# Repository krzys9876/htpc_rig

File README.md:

# Home entertainment rig

This is a dump of various files related to the devices that I use in my home entertainment setup. 

## HTPC

A miniITX PC enclosed in custom case (see: [modushop.pl](https://www.modushop.pl/)). The PC is fanless, so I had to choose a relative low power processor and a good radiator. However, since I have a overhead projector with a loud fan it doesn't matter at all.

## Volumio player

A Raspberry Pi based Volumio player (see: [volumio.com](https://volumio.com)) enclosed in custom case. There are two Pis: one is a controller for two displays, the other is the actual player.

The controller uses a quick and dirty python script (it needs refactoring and one day I will do it).

## Power amp

Generally it works but I had to remove the power meters as it wasn't a good idea. Now I'm thinking about something different.

## Power supply

This was done just for fun - two DC suppies (5V, 12V) in a custom case with meters and fancy switches. Nothing super complicated, I just wanted to have a power supply of a concise look instead of a bunch of random wall socket supplies.

## Preamp

The purpose of this was actually to make a super fancy relay-based attenuator with custom arduino-like controller. So much fun when building, maybe not that much when using it but who cares, this is what DIY is all about.

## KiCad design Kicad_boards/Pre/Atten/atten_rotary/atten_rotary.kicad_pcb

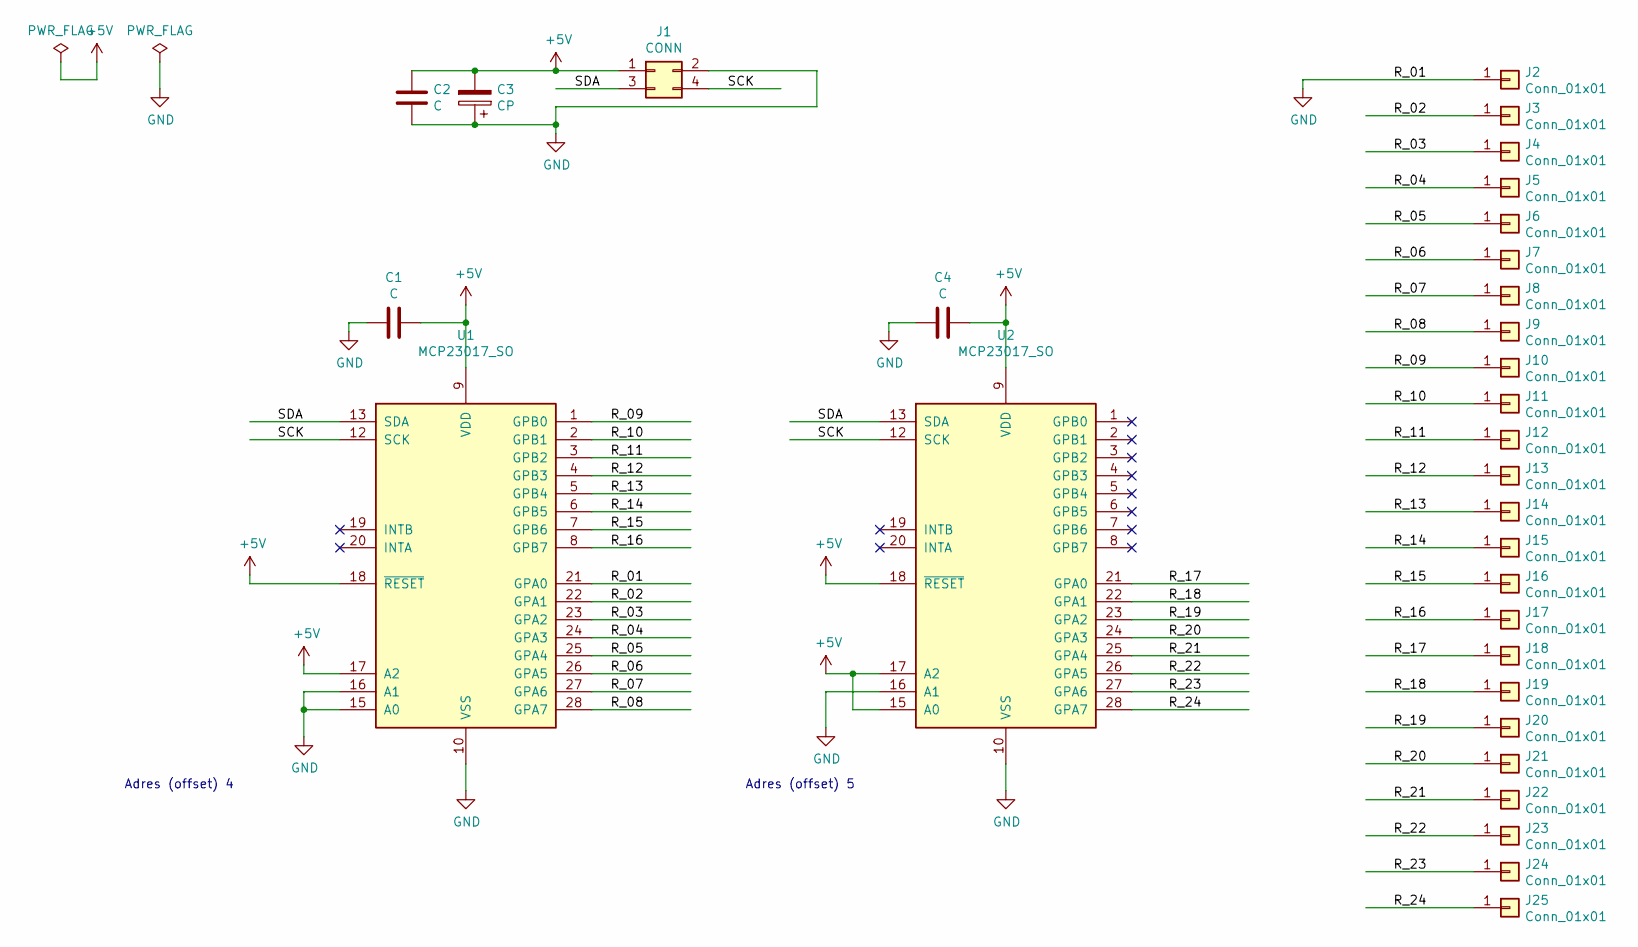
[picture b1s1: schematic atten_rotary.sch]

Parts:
C1, C2, C4: C; C_1206_3216Metric
C3: CP; C_1812_4532Metric
J1: CONN; PinHeader_2x02_P2.54mm_Vertical
J2, J3, J4, J5, J6, J7, J8, J9, J10, J11, J12, J13, J14, J15, J16, J17, J18, J19, J20, J21, J22, J23, J24, J25: Conn_01x01; PinHeader_1x01_P2.54mm_Vertical
U1, U2: MCP23017_SO; SOIC-28W_7.5x17.9mm_P1.27mm

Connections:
+5V: C1.2, C2.1, C3.2, C4.2, J1.1, U1.9 (VDD), U1.17 (A2), U1.18 (~RESET~), U2.9 (VDD), U2.15 (A0), U2.17 (A2), U2.18 (~RESET~)
/R_02: J3.1, U1.22 (GPA1)
/R_03: J4.1, U1.23 (GPA2)
/R_04: J5.1, U1.24 (GPA3)
/R_05: J6.1, U1.25 (GPA4)
/R_06: J7.1, U1.26 (GPA5)
/R_07: J8.1, U1.27 (GPA6)
/R_08: J9.1, U1.28 (GPA7)
/R_09: J10.1, U1.1 (GPB0)
/R_10: J11.1, U1.2 (GPB1)
/R_11: J12.1, U1.3 (GPB2)
/R_12: J13.1, U1.4 (GPB3)
/R_13: J14.1, U1.5 (GPB4)
/R_14: J15.1, U1.6 (GPB5)
/R_15: J16.1, U1.7 (GPB6)
/R_16: J17.1, U1.8 (GPB7)
/R_17: J18.1, U2.21 (GPA0)
/R_18: J19.1, U2.22 (GPA1)
/R_19: J20.1, U2.23 (GPA2)
/R_20: J21.1, U2.24 (GPA3)
/R_21: J22.1, U2.25 (GPA4)
/R_22: J23.1, U2.26 (GPA5)
/R_23: J24.1, U2.27 (GPA6)
/R_24: J25.1, U2.28 (GPA7)
/SCK: J1.4, U1.12 (SCK), U2.12 (SCK)
/SDA: J1.3, U1.13 (SDA), U2.13 (SDA)
GND: C1.1, C2.2, C3.1, C4.1, J1.2, J2.1, U1.10 (VSS), U1.15 (A0), U1.16 (A1), U1.21 (GPA0), U2.10 (VSS), U2.16 (A1); also elsewhere on the board

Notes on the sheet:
Adres (offset) 5
Adres (offset) 4

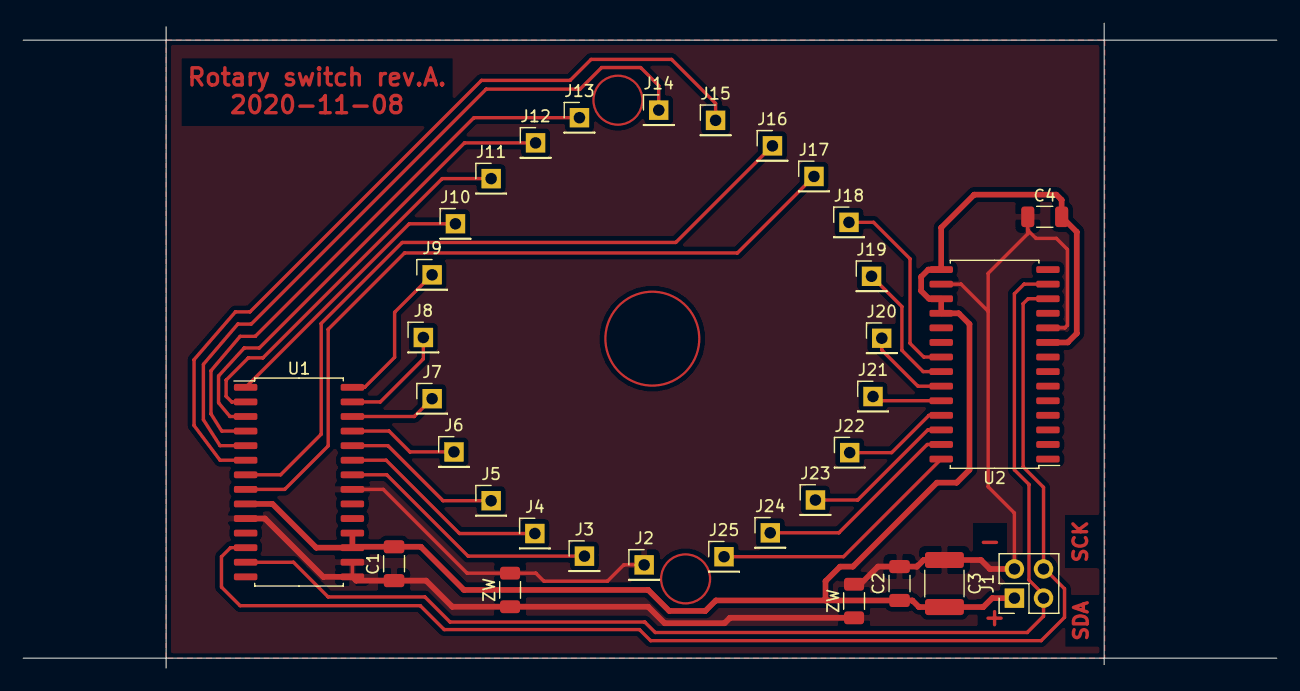
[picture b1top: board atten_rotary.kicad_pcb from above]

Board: 2 copper layers, 109.2 x 56.2 mm, 33 parts (0 on the bottom side), 27 nets.

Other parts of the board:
ZW: R_1206_3216Metric
ZW#2: 0; R_1206_3216Metric

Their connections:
GND: ZW.1, ZW.2, ZW#2.1, ZW#2.2; also elsewhere on the board

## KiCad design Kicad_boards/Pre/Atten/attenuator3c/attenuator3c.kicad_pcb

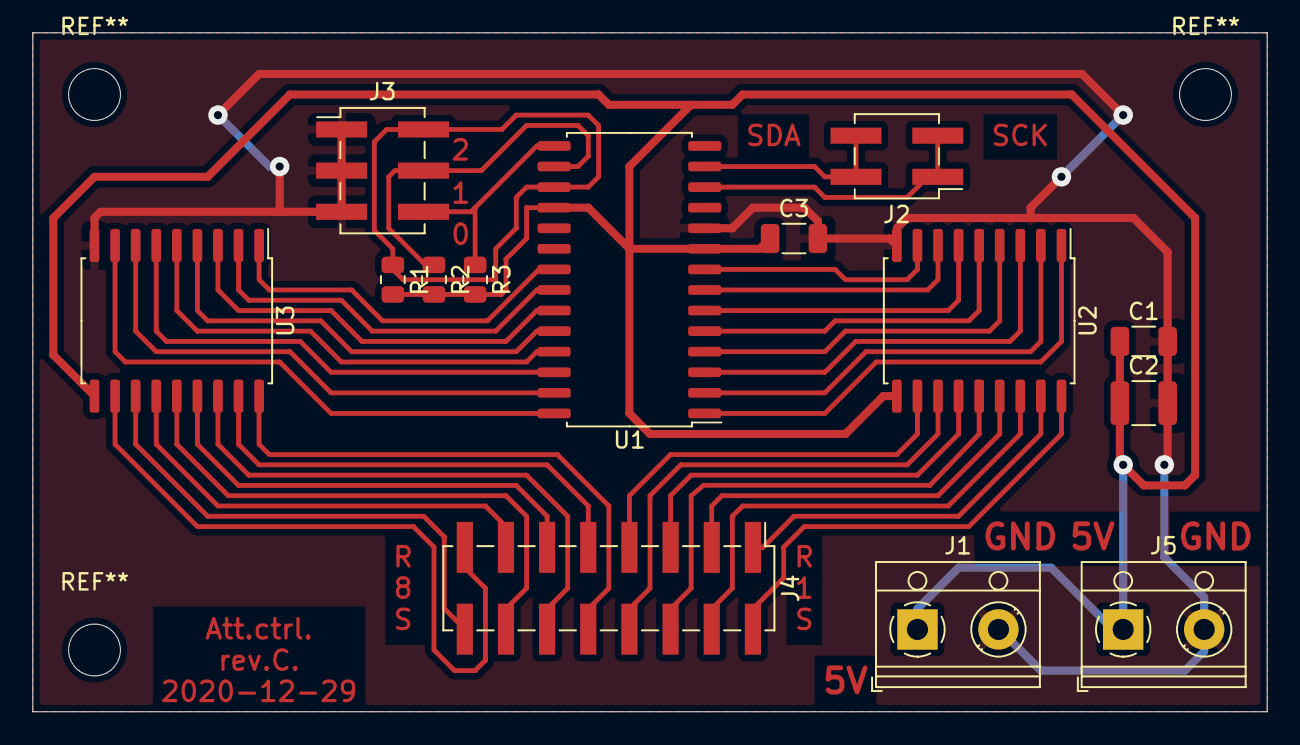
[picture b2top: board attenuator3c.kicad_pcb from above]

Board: 2 copper layers, 76.2 x 41.9 mm, 14 parts (0 on the bottom side), 39 nets.

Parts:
C1, C3: 100n; C_1206_3216Metric
C2: 10u; C_1210_3225Metric
J1: POWER; TerminalBlock_RND_205-00012_1x02_P5.00mm_Horizontal
J2: I2C; PinHeader_2x02_P2.54mm_Vertical_SMD
J3: Conn_Addr; PinHeader_2x03_P2.54mm_Vertical_SMD
J4: RELAY; PinHeader_2x08_P2.54mm_Vertical_SMD
J5: POWER2; TerminalBlock_RND_205-00012_1x02_P5.00mm_Horizontal
R1, R2, R3: R; R_0805_2012Metric
U1: MCP23017_SO; SOIC-28W_7.5x17.9mm_P1.27mm
U2, U3: ULN2803A; SOIC-18W_7.5x11.6mm_P1.27mm

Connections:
+5V: C1.1, C2.1, C3.1, J1.1, J5.1, R1.2, R2.2, R3.2, U1.9, U1.18, U2.10, U3.10
/R1_R: J4.1, U2.17
/R1_S: J4.2, U2.18
/R2_R: J4.3, U2.15
/R2_S: J4.4, U2.16
/R3_R: J4.5, U2.13
/R3_S: J4.6, U2.14
/R4_R: J4.7, U2.11
/R4_S: J4.8, U2.12
/R5_R: J4.9, U3.17
/R5_S: J4.10, U3.18
/R6_R: J4.11, U3.15
/R6_S: J4.12, U3.16
/R7_R: J4.13, U3.13
/R7_S: J4.14, U3.14
/R8_R: J4.15, U3.11
/R8_S: J4.16, U3.12
/SCK: J2.1, J2.3, U1.12
/SDA: J2.2, J2.4, U1.13
GND: C1.2, C2.2, C3.2, J1.2, J3.1, J3.3, J3.5, J5.2, U1.10, U2.9, U3.9
unnamed: J3.2, R1.1, U1.17
unnamed: J3.4, R2.1, U1.16
unnamed: J3.6, R3.1, U1.15
unnamed: U1.1, U2.1
unnamed: U1.2, U2.2
unnamed: U1.3, U2.3
unnamed: U1.4, U2.4
unnamed: U1.5, U2.5
unnamed: U1.6, U2.6
unnamed: U1.7, U2.7
unnamed: U1.8, U2.8
unnamed: U1.21, U3.1
unnamed: U1.22, U3.2
unnamed: U1.23, U3.3
unnamed: U1.24, U3.4
unnamed: U1.25, U3.5
unnamed: U1.26, U3.6
unnamed: U1.27, U3.7
unnamed: U1.28, U3.8

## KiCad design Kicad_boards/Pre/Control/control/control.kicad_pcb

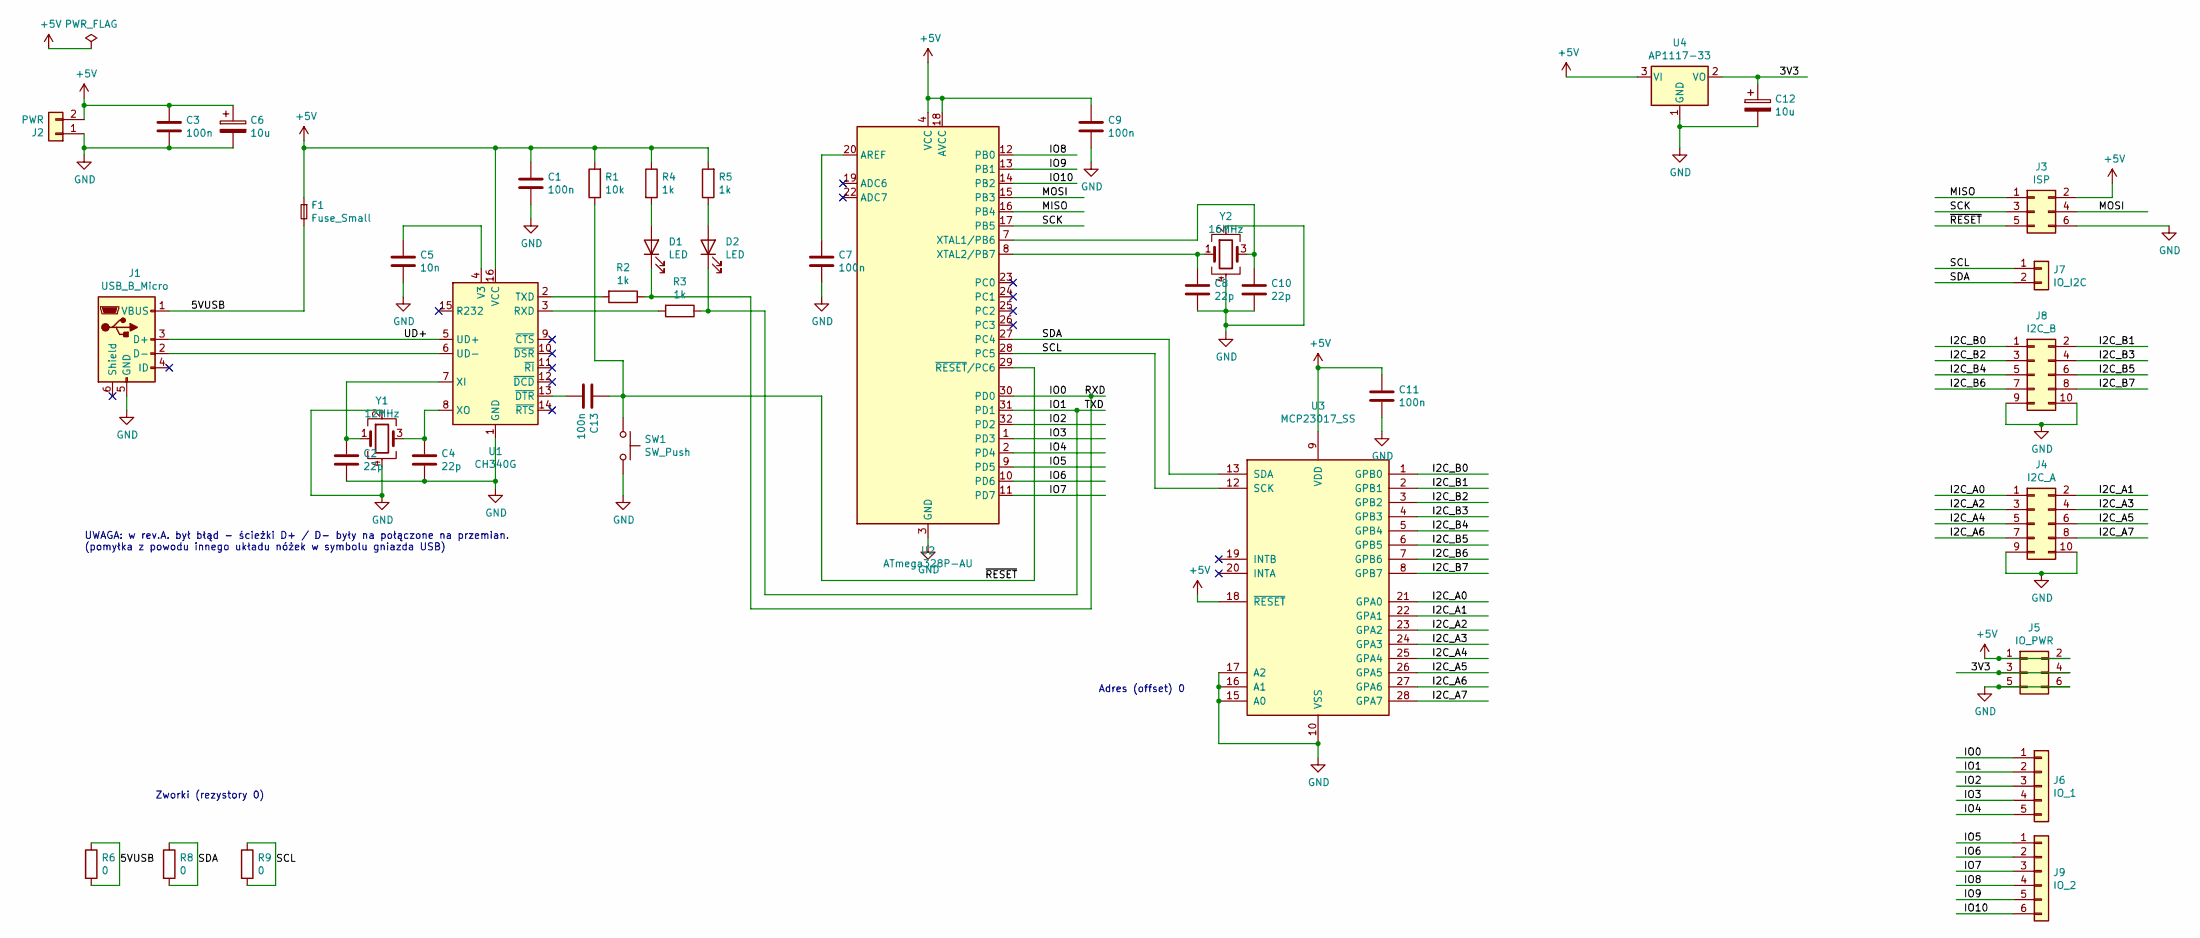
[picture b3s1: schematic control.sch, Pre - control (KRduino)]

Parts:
C1, C3, C7, C9, C11: 100n; C_1206_3216Metric
C2, C4, C8, C10: 22p; C_0603_1608Metric
C5: 10n; C_1206_3216Metric
C6, C12: 10u; C_1206_3216Metric
C13: 100n; C_0805_2012Metric
D1, D2: LED; D_0805_2012Metric
F1: Fuse_Small; Fuse_1812_4532Metric
J1: USB_B_Micro; USB_Micro-B_Amphenol_10104110_Horizontal
J2: PWR; TerminalBlock_RND_205-00001_1x02_P5.00mm_Horizontal
J3: ISP; PinHeader_2x03_P2.54mm_Vertical
J4: I2C_A; PinHeader_2x05_P2.54mm_Vertical
J5: IO_PWR; PinHeader_2x03_P2.54mm_Vertical
J6: IO_1; PinHeader_1x05_P2.54mm_Vertical
J7: IO_I2C; PinHeader_1x02_P2.54mm_Vertical
J8: I2C_B; PinHeader_2x05_P2.54mm_Vertical
J9: IO_2; PinHeader_1x06_P2.54mm_Vertical
R1: 10k; R_0805_2012Metric
R2, R3, R4, R5: 1k; R_0805_2012Metric
R6, R8, R9: 0; R_0805_2012Metric
SW1: SW_Push; SW_SPST_FSMSM
U1: CH340G; SOIC-16_3.9x9.9mm_P1.27mm
U2: ATmega328P-AU; TQFP-32_7x7mm_P0.8mm
U3: MCP23017_SS; SSOP-28_5.3x10.2mm_P0.65mm
U4: AP1117-33; SOT-223-3_TabPin2
Y1: 12MHz; Crystal_SMD_3225-4Pin_3.2x2.5mm
Y2: 16MHz; Crystal_SMD_3225-4Pin_3.2x2.5mm

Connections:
+5V: C1.1, C3.1, C6.1, C9.1, C11.1, F1.1, J2.2, J3.2, J5.1, J5.2, R1.2, R4.1, R5.2, U1.16 (VCC), U2.4 (VCC), U2.6 (VCC), U2.18 (AVCC), U3.9 (VDD), U3.18 (~RESET~), U4.3 (VI)
/3V3: C12.1, J5.3, J5.4, U4.2 (VO)
/5VUSB: F1.2, J1.1 (VBUS), R6.1, R6.2
/I2C_A0: J4.1, U3.21 (GPA0)
/I2C_A1: J4.2, U3.22 (GPA1)
/I2C_A2: J4.3, U3.23 (GPA2)
/I2C_A3: J4.4, U3.24 (GPA3)
/I2C_A4: J4.5, U3.25 (GPA4)
/I2C_A5: J4.6, U3.26 (GPA5)
/I2C_A6: J4.7, U3.27 (GPA6)
/I2C_A7: J4.8, U3.28 (GPA7)
/I2C_B0: J8.1, U3.1 (GPB0)
/I2C_B1: J8.2, U3.2 (GPB1)
/I2C_B2: J8.3, U3.3 (GPB2)
/I2C_B3: J8.4, U3.4 (GPB3)
/I2C_B4: J8.5, U3.5 (GPB4)
/I2C_B5: J8.6, U3.6 (GPB5)
/I2C_B6: J8.7, U3.7 (GPB6)
/I2C_B7: J8.8, U3.8 (GPB7)
/IO0: D1.1 (K), J6.1, R2.1, U2.30 (PD0)
/IO1: D2.1 (K), J6.2, R3.1, U2.31 (PD1)
/IO2: J6.3, U2.32 (PD2)
/IO3: J6.4, U2.1 (PD3)
/IO4: J6.5, U2.2 (PD4)
/IO5: J9.1, U2.9 (PD5)
/IO6: J9.2, U2.10 (PD6)
/IO7: J9.3, U2.11 (PD7)
/IO8: J9.4, U2.12 (PB0)
/IO9: J9.5, U2.13 (PB1)
/IO10: J9.6, U2.14 (PB2)
/MISO: J3.1, U2.16 (PB4)
/MOSI: J3.4, U2.15 (PB3)
/SCK: J3.3, U2.17 (PB5)
/SCL: J7.1, R9.1, R9.2, U2.28 (PC5), U3.12 (SCK)
/SDA: J7.2, R8.1, R8.2, U2.27 (PC4), U3.13 (SDA)
/UD+: J1.3 (D+), U1.5 (UD+)
/~RESET: C13.1, J3.5, R1.1, SW1.1, U2.29 (~RESET~/PC6)
GND: C1.2, C2.2, C3.2, C4.2, C5.1, C6.2, C7.2, C8.2, C9.2, C10.2, C11.2, C12.2, J1.5 (GND), J2.1, J3.6, J4.9, J4.10, J5.5, J5.6, J8.9, J8.10, SW1.2, U1.1 (GND), U2.3 (GND), U2.5 (GND), U2.21 (GND), U3.10 (VSS), U3.15 (A0), U3.16 (A1), U3.17 (A2), U4.1 (GND), Y1.2, Y1.4, Y2.2, Y2.4
unnamed: C2.1, U1.7 (XI), Y1.1
unnamed: C4.1, U1.8 (XO), Y1.3
unnamed: C5.2, U1.4 (V3)
unnamed: C7.1, U2.20 (AREF)
unnamed: C8.1, U2.8 (XTAL2/PB7), Y2.1
unnamed: C10.1, U2.7 (XTAL1/PB6), Y2.3
unnamed: C13.2, U1.13 (~DTR)
unnamed: D1.2 (A), R4.2
unnamed: D2.2 (A), R5.1
unnamed: J1.2 (D-), U1.6 (UD-)
unnamed: R2.2, U1.2 (TXD)
unnamed: R3.2, U1.3 (RXD)

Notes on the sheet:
Zworki (rezystory 0)
UWAGA: w rev.A. był błąd - ścieżki D+ / D- były na połączone na przemian. (pomyłka z powodu innego układu nóżek w symbolu gniazda USB)
Adres (offset) 0

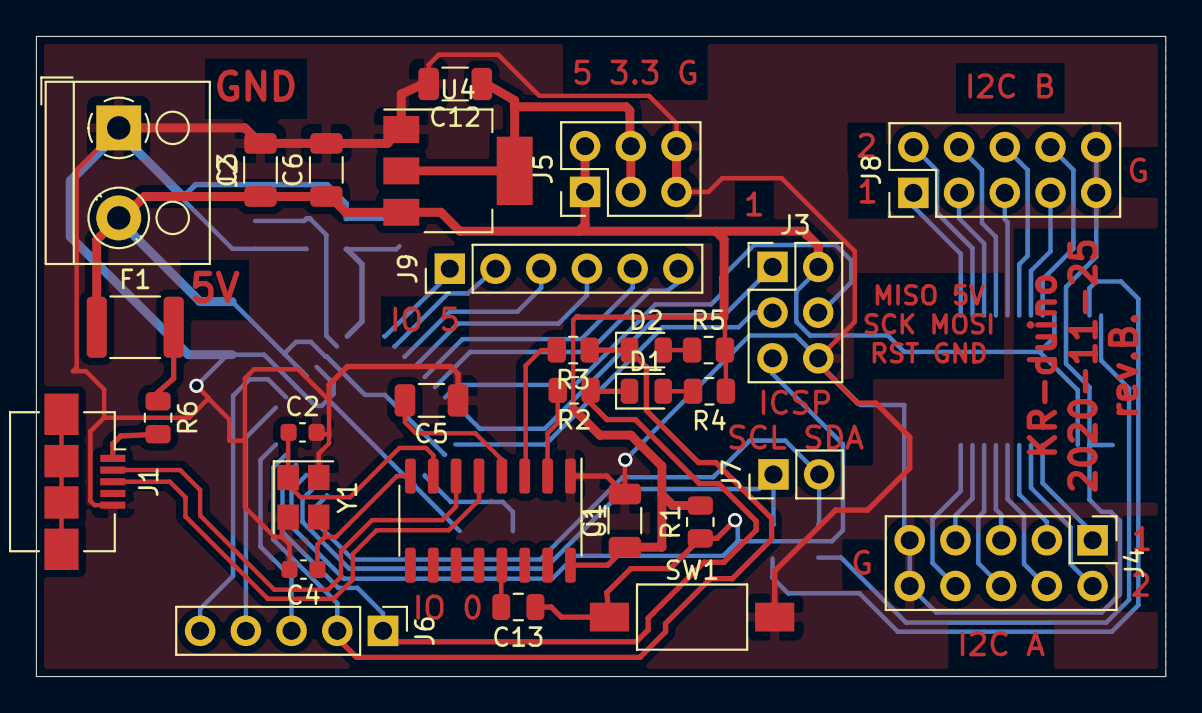
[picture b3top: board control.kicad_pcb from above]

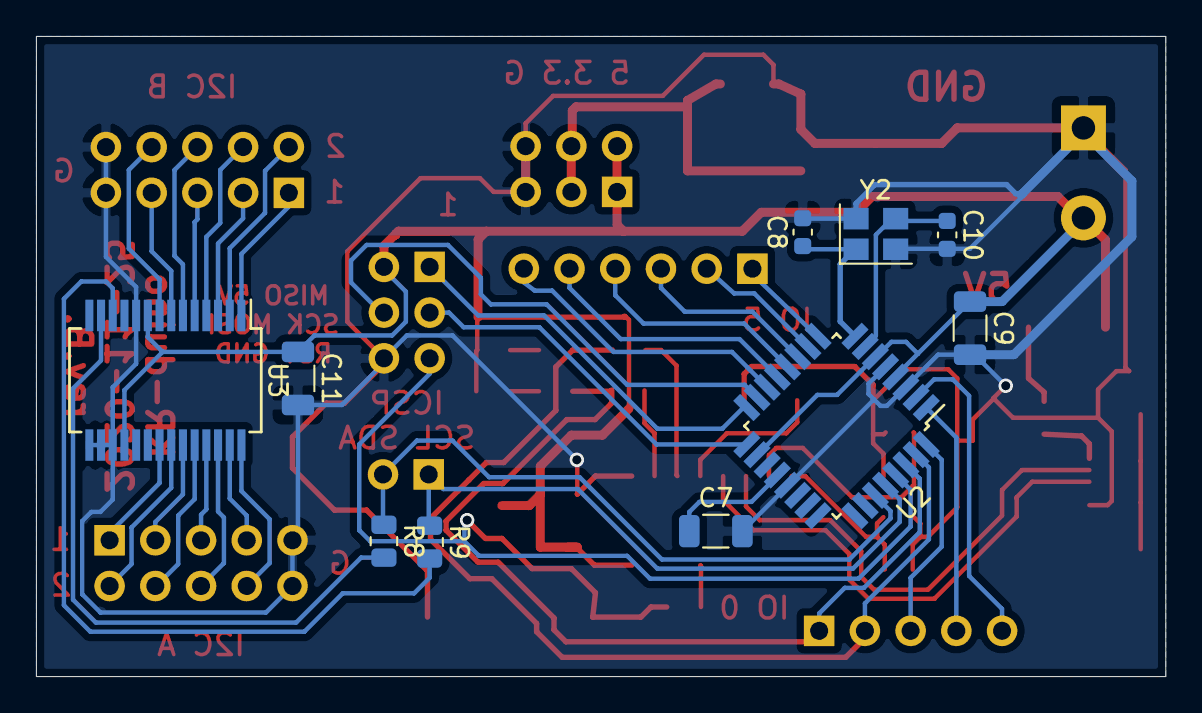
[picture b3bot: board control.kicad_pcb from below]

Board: 2 copper layers, 62.7 x 35.6 mm, 40 parts (10 on the bottom side), 50 nets.

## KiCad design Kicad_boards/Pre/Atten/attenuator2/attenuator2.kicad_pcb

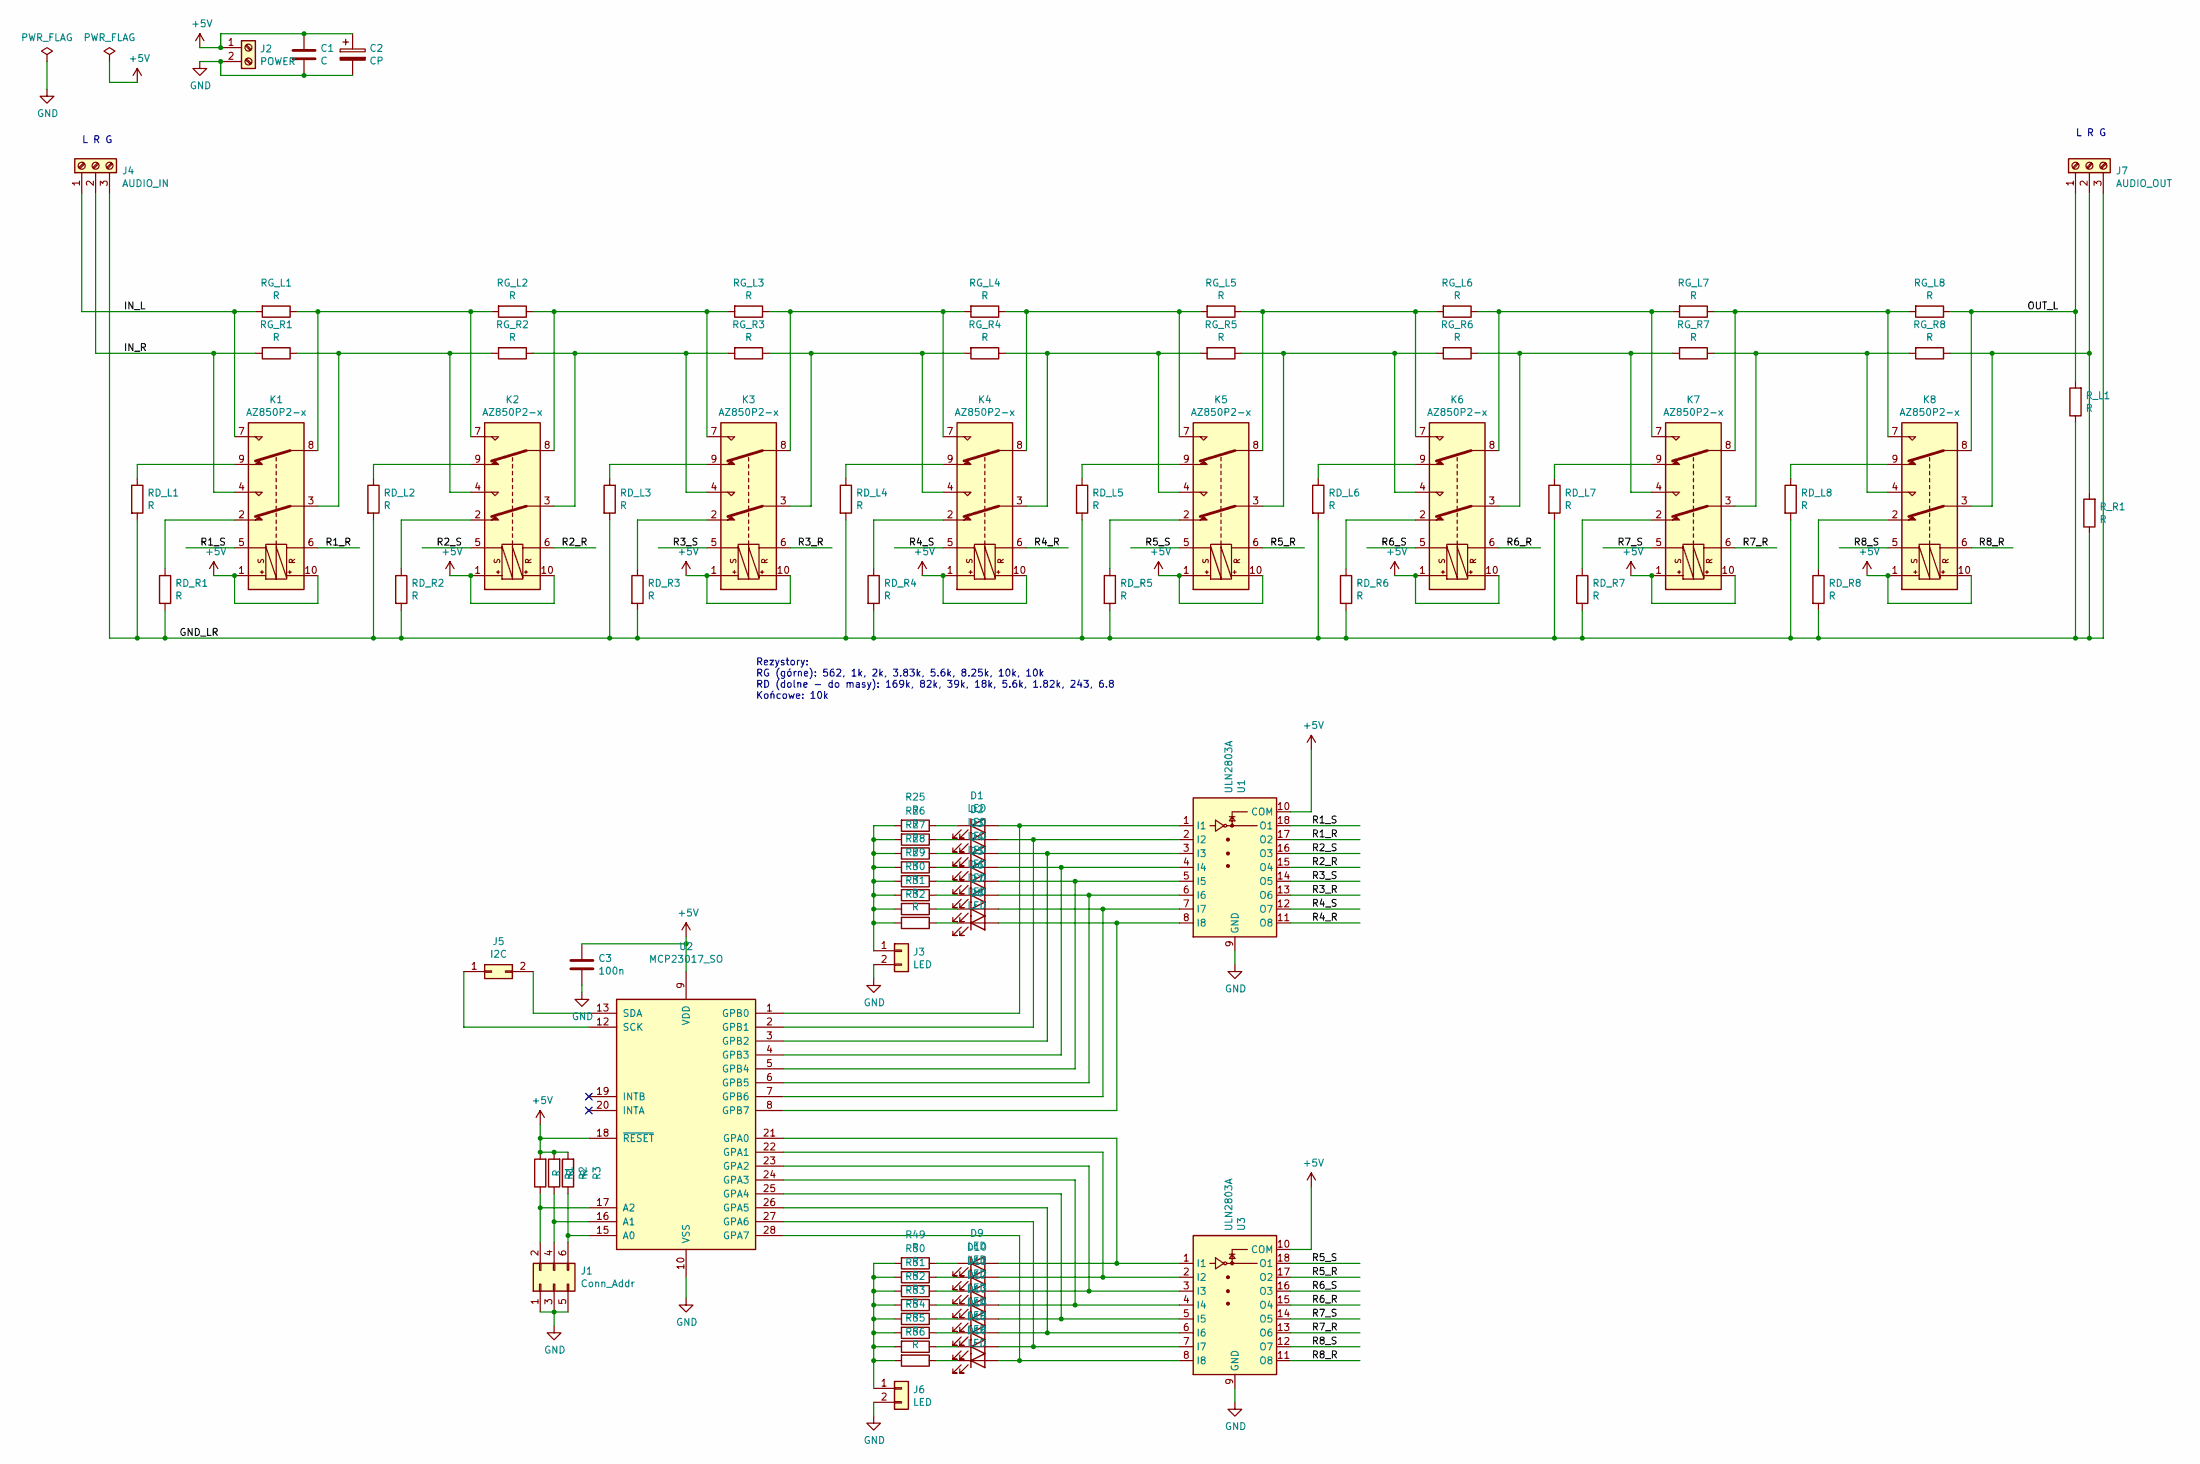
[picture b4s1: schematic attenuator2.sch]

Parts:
C1: C; C_1206_3216Metric
C2: CP; C_1210_3225Metric
C3: 100n; C_1206_3216Metric
D1, D2, D3, D4, D5, D6, D7, D8, D9, D10, D11, D12, D13, D14, D15, D16: LED; LED_0805_2012Metric
J1: Conn_Addr; PinHeader_2x03_P2.54mm_Vertical
J2: POWER; TerminalBlock_RND_205-00012_1x02_P5.00mm_Horizontal
J3, J6: LED; PinHeader_1x02_P2.54mm_Vertical
J4: AUDIO_IN; TerminalBlock_RND_205-00013_1x03_P5.00mm_Horizontal
J5: I2C; PinHeader_2x01_P2.54mm_Vertical_SMD
J7: AUDIO_OUT; TerminalBlock_RND_205-00013_1x03_P5.00mm_Horizontal
K1, K2, K3, K4, K5, K6, K7, K8: AZ850P2-x; Relay_DPDT_FRT5
R1, R2, R3, R25, R26, R27, R28, R29, R30, R31, R32, R49, R50, R51, R52, R53, R54, R55, R56: R; R_0805_2012Metric
RD_L1, RD_L2, RD_L3, RD_L4, RD_L5, RD_L6, RD_L7, RD_L8: R; R_Axial_DIN0207_L6.3mm_D2.5mm_P10.16mm_Horizontal
RD_R1, RD_R2, RD_R3, RD_R4, RD_R5, RD_R6, RD_R7, RD_R8: R; R_Axial_DIN0207_L6.3mm_D2.5mm_P10.16mm_Horizontal
RG_L1, RG_L2, RG_L3, RG_L4, RG_L5, RG_L6, RG_L7, RG_L8: R; R_Axial_DIN0207_L6.3mm_D2.5mm_P10.16mm_Horizontal
RG_R1, RG_R2, RG_R3, RG_R4, RG_R5, RG_R6, RG_R7, RG_R8: R; R_Axial_DIN0207_L6.3mm_D2.5mm_P10.16mm_Horizontal
R_L1: R; R_Axial_DIN0207_L6.3mm_D2.5mm_P10.16mm_Horizontal
R_R1: R; R_Axial_DIN0207_L6.3mm_D2.5mm_P10.16mm_Horizontal
U1, U3: ULN2803A; SOIC-18W_7.5x11.6mm_P1.27mm
U2: MCP23017_SO; SOIC-28W_7.5x17.9mm_P1.27mm

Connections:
+5V: C1.1, C2.1, C3.1, J2.1, K1.1, K1.10, K2.1, K2.10, K3.1, K3.10, K4.1, K4.10, K5.1, K5.10, K6.1, K6.10, K7.1, K7.10, K8.1, K8.10, R1.2, R2.2, R3.2, U1.10 (COM), U2.9 (VDD), U2.18 (~RESET~), U3.10 (COM)
/GND_LR: J4.3, J7.3, RD_L1.2, RD_L2.2, RD_L3.2, RD_L4.2, RD_L5.2, RD_L6.2, RD_L7.2, RD_L8.2, RD_R1.2, RD_R2.2, RD_R3.2, RD_R4.2, RD_R5.2, RD_R6.2, RD_R7.2, RD_R8.2, R_L1.1, R_R1.1
/IN_L: J4.1, K1.7, RG_L1.2
/IN_R: J4.2, K1.4, RG_R1.2
/OUT_L: J7.1, K8.8, RG_L8.1, R_L1.2
/R1_R: K1.6, U1.17 (O2)
/R1_S: K1.5, U1.18 (O1)
/R2_R: K2.6, U1.15 (O4)
/R2_S: K2.5, U1.16 (O3)
/R3_R: K3.6, U1.13 (O6)
/R3_S: K3.5, U1.14 (O5)
/R4_R: K4.6, U1.11 (O8)
/R4_S: K4.5, U1.12 (O7)
/R5_R: K5.6, U3.17 (O2)
/R5_S: K5.5, U3.18 (O1)
/R6_R: K6.6, U3.15 (O4)
/R6_S: K6.5, U3.16 (O3)
/R7_R: K7.6, U3.13 (O6)
/R7_S: K7.5, U3.14 (O5)
/R8_R: K8.6, U3.11 (O8)
/R8_S: K8.5, U3.12 (O7)
GND: C1.2, C2.2, C3.2, J1.1, J1.3, J1.5, J2.2, J3.2, J6.2, U1.9 (GND), U2.10 (VSS), U3.9 (GND)
unnamed: D1.1 (K), R25.1
unnamed: D1.2 (A), U1.1 (I1), U2.1 (GPB0)
unnamed: D2.1 (K), R26.1
unnamed: D2.2 (A), U1.2 (I2), U2.2 (GPB1)
unnamed: D3.1 (K), R27.1
unnamed: D3.2 (A), U1.3 (I3), U2.3 (GPB2)
unnamed: D4.1 (K), R28.1
unnamed: D4.2 (A), U1.4 (I4), U2.4 (GPB3)
unnamed: D5.1 (K), R29.1
unnamed: D5.2 (A), U1.5 (I5), U2.5 (GPB4)
unnamed: D6.1 (K), R30.1
unnamed: D6.2 (A), U1.6 (I6), U2.6 (GPB5)
unnamed: D7.1 (K), R31.1
unnamed: D7.2 (A), U1.7 (I7), U2.7 (GPB6)
unnamed: D8.1 (K), R32.1
unnamed: D8.2 (A), U1.8 (I8), U2.8 (GPB7)
unnamed: D9.1 (K), R49.1
unnamed: D9.2 (A), U2.21 (GPA0), U3.1 (I1)
unnamed: D10.1 (K), R50.1
unnamed: D10.2 (A), U2.22 (GPA1), U3.2 (I2)
unnamed: D11.1 (K), R51.1
unnamed: D11.2 (A), U2.23 (GPA2), U3.3 (I3)
unnamed: D12.1 (K), R52.1
unnamed: D12.2 (A), U2.24 (GPA3), U3.4 (I4)
unnamed: D13.1 (K), R53.1
unnamed: D13.2 (A), U2.25 (GPA4), U3.5 (I5)
unnamed: D14.1 (K), R54.1
unnamed: D14.2 (A), U2.26 (GPA5), U3.6 (I6)
unnamed: D15.1 (K), R55.1
unnamed: D15.2 (A), U2.27 (GPA6), U3.7 (I7)
unnamed: D16.1 (K), R56.1
unnamed: D16.2 (A), U2.28 (GPA7), U3.8 (I8)
unnamed: J1.2, R1.1, U2.17 (A2)
unnamed: J1.4, R2.1, U2.16 (A1)
unnamed: J1.6, R3.1, U2.15 (A0)
unnamed: J3.1, R25.2, R26.2, R27.2, R28.2, R29.2, R30.2, R31.2, R32.2
unnamed: J5.1, U2.12 (SCK)
unnamed: J5.2, U2.13 (SDA)
unnamed: J6.1, R49.2, R50.2, R51.2, R52.2, R53.2, R54.2, R55.2, R56.2
unnamed: J7.2, K8.3, RG_R8.1, R_R1.2
unnamed: K1.2, RD_R1.1
unnamed: K1.3, K2.4, RG_R1.1, RG_R2.2
unnamed: K1.8, K2.7, RG_L1.1, RG_L2.2
unnamed: K1.9, RD_L1.1
unnamed: K2.2, RD_R2.1
unnamed: K2.3, K3.4, RG_R2.1, RG_R3.2
unnamed: K2.8, K3.7, RG_L2.1, RG_L3.2
unnamed: K2.9, RD_L2.1
unnamed: K3.2, RD_R3.1
unnamed: K3.3, K4.4, RG_R3.1, RG_R4.2
unnamed: K3.8, K4.7, RG_L3.1, RG_L4.2
unnamed: K3.9, RD_L3.1
unnamed: K4.2, RD_R4.1
unnamed: K4.3, K5.4, RG_R4.1, RG_R5.2
unnamed: K4.8, K5.7, RG_L4.1, RG_L5.2
unnamed: K4.9, RD_L4.1
unnamed: K5.2, RD_R5.1
unnamed: K5.3, K6.4, RG_R5.1, RG_R6.2
unnamed: K5.8, K6.7, RG_L5.1, RG_L6.2
unnamed: K5.9, RD_L5.1
unnamed: K6.2, RD_R6.1
unnamed: K6.3, K7.4, RG_R6.1, RG_R7.2
unnamed: K6.8, K7.7, RG_L6.1, RG_L7.2
unnamed: K6.9, RD_L6.1
unnamed: K7.2, RD_R7.1
unnamed: K7.3, K8.4, RG_R7.1, RG_R8.2
unnamed: K7.8, K8.7, RG_L7.1, RG_L8.2
unnamed: K7.9, RD_L7.1
unnamed: K8.2, RD_R8.1
unnamed: K8.9, RD_L8.1

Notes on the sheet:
Rezystory: RG (górne): 562, 1k, 2k, 3.83k, 5.6k, 8.25k, 10k, 10k RD (dolne - do masy): 169k, 82k, 39k, 18k, 5.6k, 1.82k, 243, 6.8 Końcowe: 10k
L R G

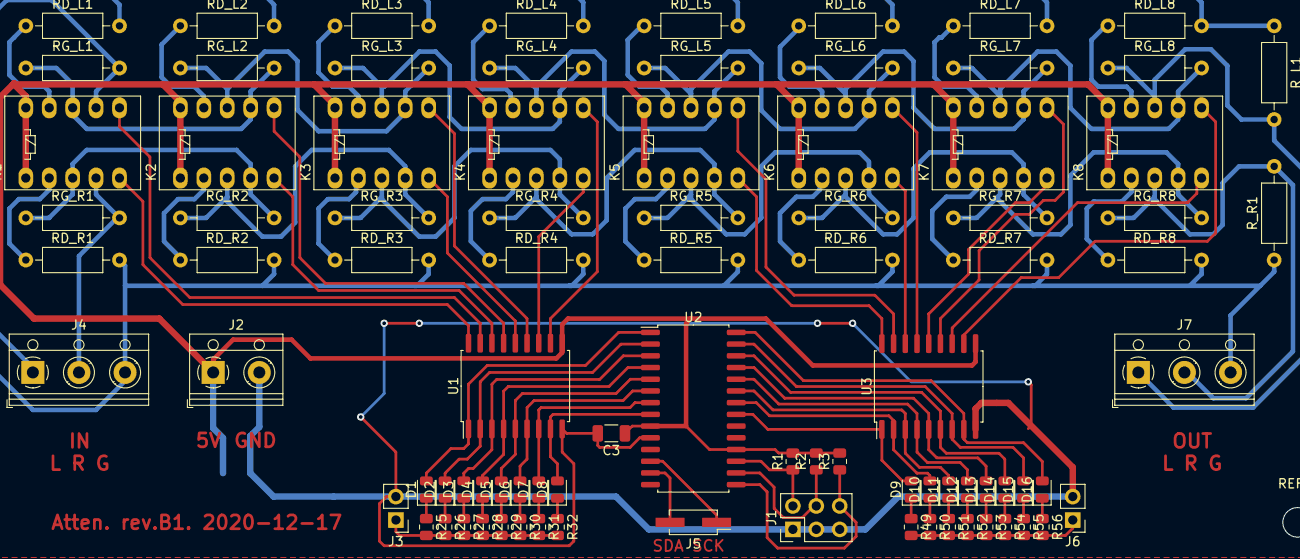
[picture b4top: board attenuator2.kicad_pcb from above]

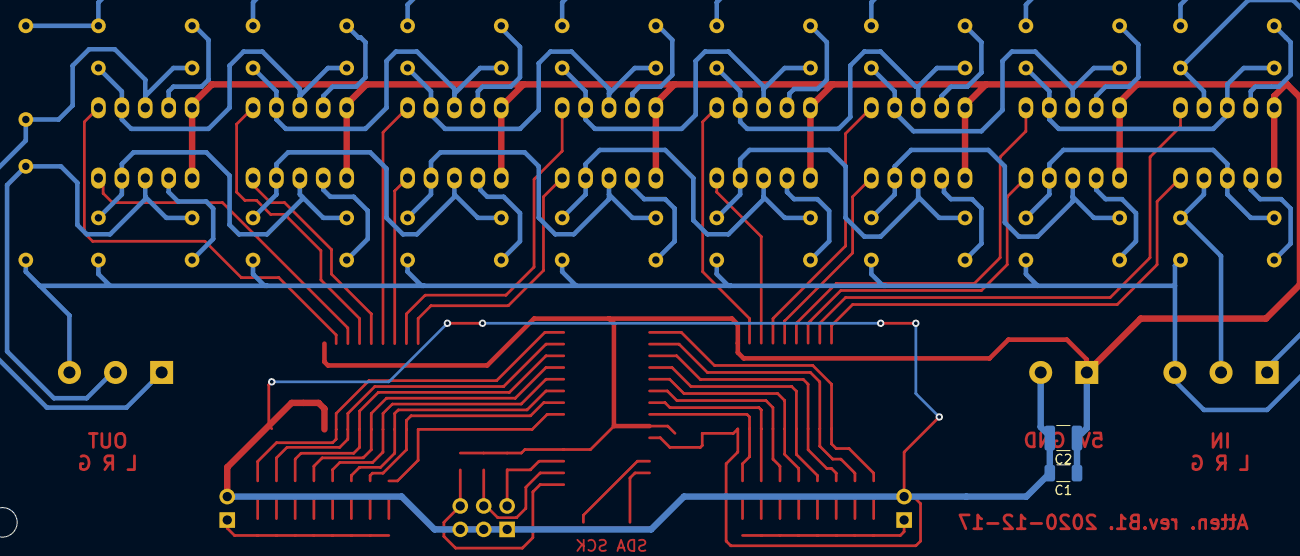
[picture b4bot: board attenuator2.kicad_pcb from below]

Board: 2 copper layers, 90 parts (2 on the bottom side), 92 nets.

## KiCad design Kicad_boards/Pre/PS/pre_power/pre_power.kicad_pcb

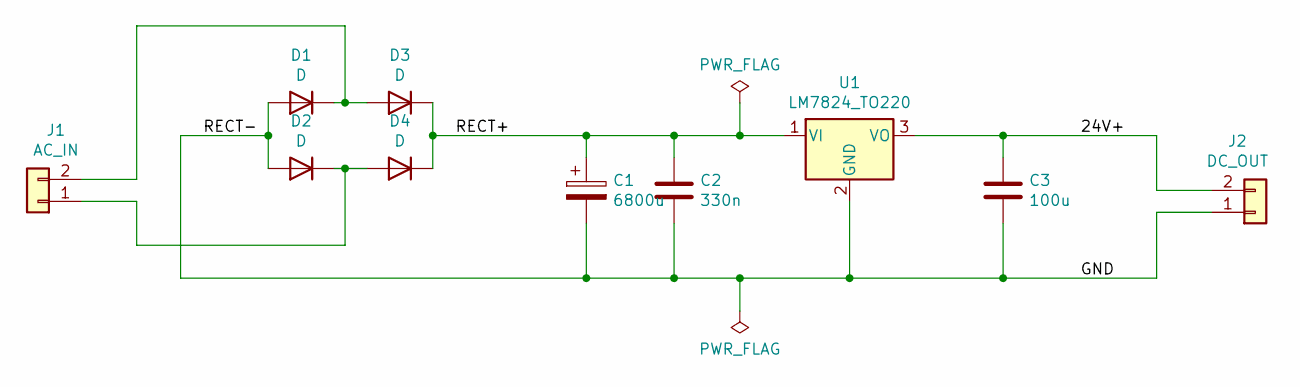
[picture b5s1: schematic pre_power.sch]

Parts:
C1: 6800u; TerminalBlock_RND_205-00001_1x02_P5.00mm_Horizontal
C2: 330n; C_Disc_D4.7mm_W2.5mm_P5.00mm
C3: 100u; C_Disc_D4.7mm_W2.5mm_P5.00mm
D1, D2, D3, D4: D; TO-220F-2_Vertical
J1: AC_IN; TerminalBlock_RND_205-00001_1x02_P5.00mm_Horizontal
J2: DC_OUT; TerminalBlock_RND_205-00001_1x02_P5.00mm_Horizontal
U1: LM7824_TO220; TO-220-3_Vertical

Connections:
/24V+: C3.1, J2.2, U1.3 (VO)
/GND: C1.2, C2.2, C3.2, D1.2 (A), D2.2 (A), J2.1, U1.2 (GND)
/RECT+: C1.1, C2.1, D3.1 (K), D4.1 (K), U1.1 (VI)
unnamed: D1.1 (K), D3.2 (A), J1.2
unnamed: D2.1 (K), D4.2 (A), J1.1

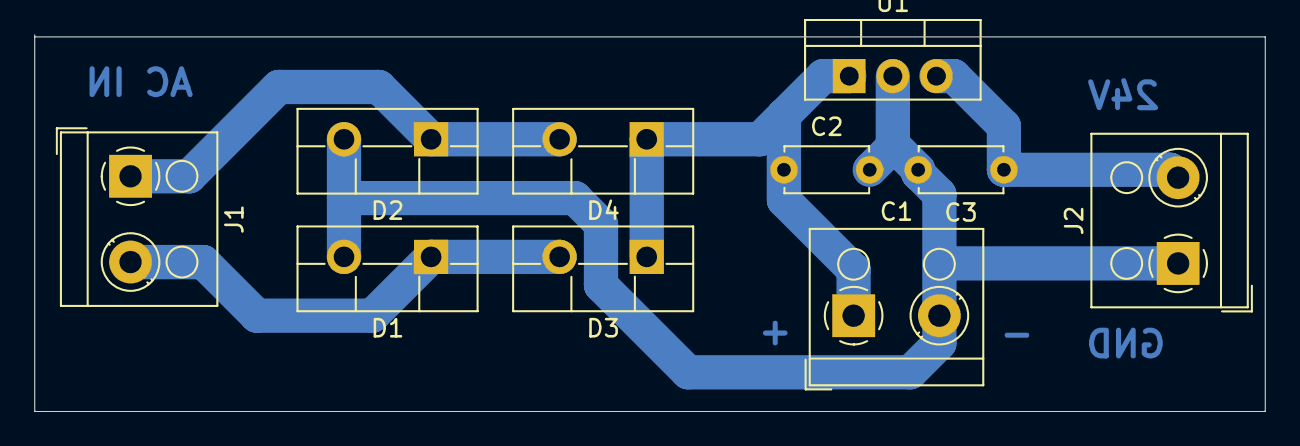
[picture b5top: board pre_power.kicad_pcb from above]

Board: 2 copper layers, 71.8 x 22.0 mm, 10 parts (0 on the bottom side), 5 nets.
